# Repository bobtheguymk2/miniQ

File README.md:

# miniQ
A PCB for model rocket datalogging and control

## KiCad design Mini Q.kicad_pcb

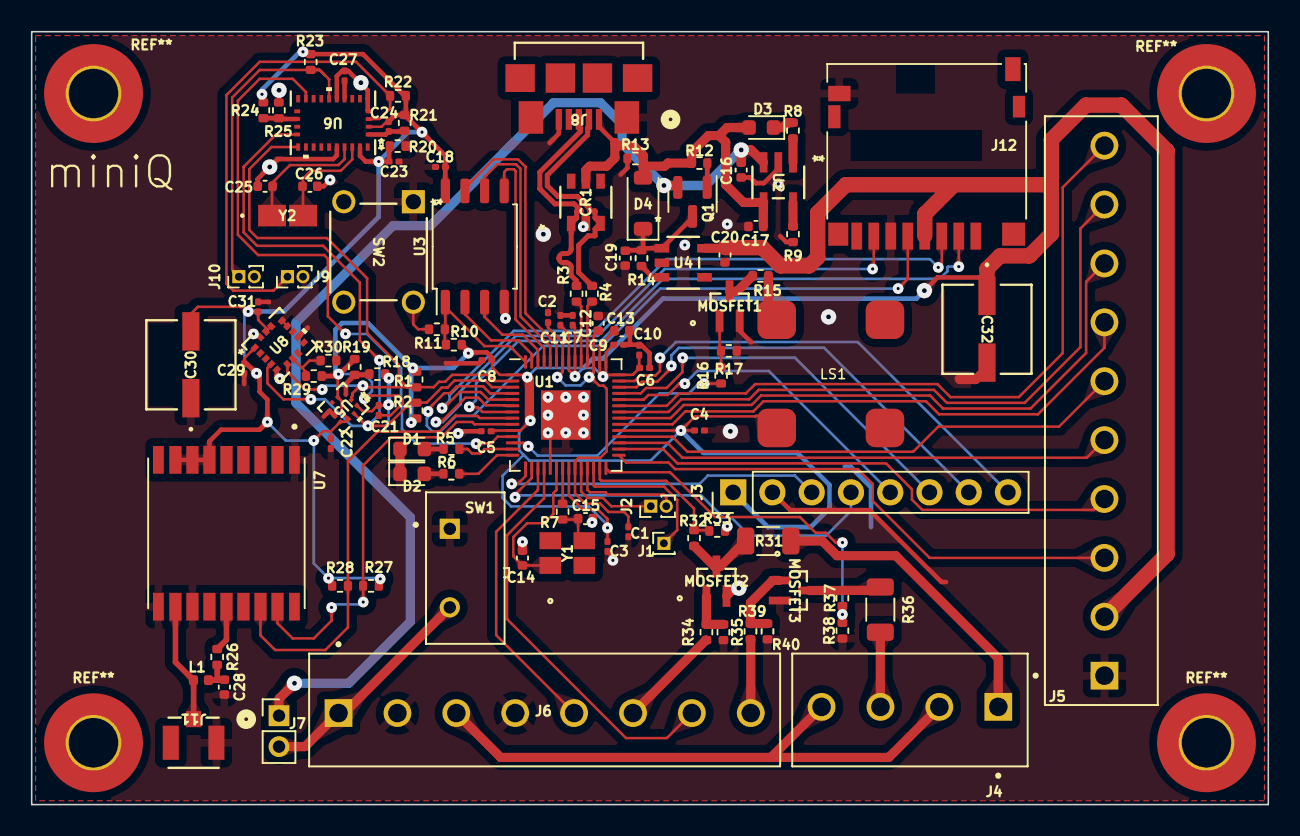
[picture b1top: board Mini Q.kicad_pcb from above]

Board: 2 copper layers, 80.0 x 50.0 mm, 107 parts (0 on the bottom side), 84 nets.

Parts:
C1, C2, C3, C4, C5, C6, C7, C8, C9, C10, C11, C18, C21, C22, C23, C24, C27, C29, C31: 100n; C_0201_0603Metric
C12, C13: 1u; C_0402_1005Metric
C14, C15, C25, C26: 15p; C_0402_1005Metric
C16, C17, C19, C20: 10u; C_0402_1005Metric
C28: 10n; C_0402_1005Metric
C30, C32: 10u; CAP_B6-SVPK_PAN-L
CR1: USBLC6-4SC6; SOT23-6L_STM
D1, D2, D3: LED; D_0603_1608Metric
D4: MBR0540; D_SOD-123
J1: Conn_01x01; PinHeader_1x01_P1.00mm_Vertical
J2: Conn_01x02; PinHeader_1x02_P1.00mm_Vertical
J3: Conn_01x08; PinHeader_1x08_P2.54mm_Vertical
J4: Pyro_Screw_Terminal_01x04; TE_1776113-4
J5: Screw_Terminal_01x10; TE_1-1776113-0
J6: Screw_Terminal_01x08; TE_1776113-8
J7: PH2.0 Female for LiPo; PinHeader_1x02_P2.00mm_Vertical
J8: USB_B_Micro; CONN_10118192-0002LF_AMP
J9: BNO_BTLDR; PinHeader_1x02_P1.00mm_Vertical
J10: BNO_NRST; PinHeader_1x02_P1.00mm_Vertical
J11: UFL Connector; CONN_RSP-122811-01_SAI
J12: Micro_SD_Card; microSD_HC_Hirose_DM3D-SF
L1: 27n; L_0402_1005Metric
LS1: TE084005-2
MOSFET1, MOSFET2, MOSFET3: DMN2058UW-7; SOT323_DMN2058UW_DIO-M
Q1: DMG3414U; SOT-23
R1, R2: 4.7k; R_0402_1005Metric
R3, R4: 27.4; R_0402_1005Metric
R5, R6: 430; R_0402_1005Metric
R7, R11, R12: 1k; R_0402_1005Metric
R8, R10, R13, R14, R17, R22, R23, R24, R29, R35, R40: 10k; R_0402_1005Metric
R9: 5.1k; R_0402_1005Metric
R15: 33; R_0402_1005Metric
R16, R34, R39: 400; R_0402_1005Metric
R18, R19, R25, R30: 0; R_0402_1005Metric
R20, R21, R27, R28: DNF; R_0402_1005Metric
R26: 10; R_0402_1005Metric
R31, R36: 6; R_1206_3216Metric
R32, R37: 100k; R_0402_1005Metric
R33, R38: 27k; R_0402_1005Metric
SW1: SW_SPST; SW_AS11CP
SW2: SW_Push; SW4_1825910-B_TEC
U1: RP2040; QFN-56-1EP_7x7mm_P0.4mm_EP3.2x3.2mm
U2: MCP73831T-2ACI/OT; SOT-23-5_MC_MCH
U3: W25Q128JVS; SOIC-8_5.23x5.23mm_P1.27mm
U4: RT9080-33GJ5; TSOT-23-5_RIT
U5: BMP390; LGA10_BMP390_BOS
U6: BNO086; QFN28_BNO086_CEV
U7: MAX-M8C-0; XCVR_MAX-M8C-0
U8: H3LIS200DLTR; TFLGA_S200DL_STM
Y1: ABM8-272-T3 -12.000MHZ; ABM8-272-T3_ABR
Y2: 32.768kHz Crystal; RT3215_RAL-M

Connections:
+1V1: C1.1, C2.1, C12.1, U1.23 (DVDD), U1.45 (VREG_VOUT), U1.50 (DVDD)
+3V3: C3.1, C4.1, C5.1, C6.1, C7.1, C8.1, C9.1, C10.1, C11.1, C13.1, C18.1, C20.1, C21.1, C22.1, C23.2, C24.2, C29.2, C30.2, C31.2, C32.1, J3.1, J5.2, J12.4 (VDD), LS1.2, R1.1, R2.1, R10.2, R19.1, R20.1, R21.1, R22.2, R23.2, R24.1, R27.1, R28.1, R29.1, U1.1 (IOVDD), U1.10 (IOVDD), U1.22 (IOVDD), U1.33 (IOVDD), U1.42 (IOVDD), U1.43 (ADC_AVDD), U1.44 (VREG_IN), U1.48 (USB_VDD), U1.49 (IOVDD), U3.8 (VCC), U4.5 (VOUT), U5.1 (VDDIO), U5.6 (CSB), U5.10 (VDD), U6.3 (VDD), U6.28 (VDDIO), U7.6 (V_BCKP), U7.7 (VCC_IO), U7.8 (VCC), U8.1 (Vdd_IO), U8.14 (Vdd), U8.15 (Reserved)
+12V: J4.2, J4.4, J6.3
+BATT: C16.1, J7.1, Q1.2 (S), U2.3 (VBAT)
/GPIO18_PWM1A_TVC/FINS: J5.3, U1.29 (GPIO18)
/GPIO19_PWM1B_TVC/FINS: J5.4, U1.30 (GPIO19)
/GPIO20_PWM2A_TVC/FINS: J5.5, U1.31 (GPIO20)
/GPIO21_PWM2B_TVC/FINS: J5.6, U1.32 (GPIO21)
/GPIO22_PWM3A_TVC/FINS: J5.7, U1.34 (GPIO22)
/GPIO23_PWM3B_TVC/FINS: J5.8, U1.35 (GPIO23)
/GPIO24_PWM4A_ROLL: J5.9, U1.36 (GPIO24)
/GPIO25_PWM4B_ROLL: J5.10, U1.37 (GPIO25)
/QSPI_SCLK: U1.52 (QSPI_SCLK), U3.6 (CLK)
/QSPI_SD0: U1.53 (QSPI_SD0), U3.5 (DI(IO0))
/QSPI_SD1: U1.55 (QSPI_SD1), U3.2 (DO(IO1))
/QSPI_SD2: U1.54 (QSPI_SD2), U3.3 (IO2)
/QSPI_SD3: U1.51 (QSPI_SD3), U3.7 (IO3)
/QSPI_SS: R10.1, R11.2, U1.56 (QSPI_SS), U3.1 (~CS)
/SWTCH+: J6.1, J7.2, SW1.3 (B)
/USB_D+: CR1.1 (I/O1), J8.3 (D+), R3.1
/USB_D-: CR1.3 (I/O2), J8.2 (D-), R4.1
Fet_apogee: J4.1, R31.2
Fet_apogee_sense: R32.2, R33.1, U1.27 (GPIO16)
Fet_main: J4.3, R36.2
Fet_main_sense: R37.2, R38.1, U1.28 (GPIO17)
GND: C1.2, C2.2, C3.2, C4.2, C5.2, C6.2, C7.2, C8.2, C9.2, C10.2, C11.2, C12.2, C13.2, C14.2, C15.2, C16.2, C17.2, C18.2, C19.2, C20.2, C21.2, C22.2, C23.1, C24.1, C25.2, C26.2, C27.2, C28.2, C29.1, C30.1, C31.1, C32.2, CR1.2 (GND), D1.1 (K), D2.1 (K), J3.2, J5.1, J6.2, J6.4, J8.5 (GND), J8.6 (Shield), J9.2, J10.2, J11.2 (Ext), J12.6 (VSS), J12.9 (SHIELD), MOSFET1.2 (S), MOSFET2.2 (S), MOSFET3.2 (S), R9.2, R13.1, R17.1, R18.2, R20.2, R21.2, R25.2, R30.2, R33.2, R35.1, R38.2, R40.1, SW1.1 (A), SW2.1, U1.19 (TESTEN), U1.57 (GND), U2.2 (VSS), U3.4 (GND), U4.2 (GND), U5.3 (VSS), U5.8 (VSS), U5.9 (VSS), U6.2 (GND), U6.5 (PS1), U6.6 (PS0/WAKE), U6.10 (CLKSEL0), U6.25 (GND), U7.1 (GND), U7.10 (GND), U7.12 (GND), U8.5 (GND), U8.10 (Reserved), U8.12 (GND), U8.13 (GND), U8.16 (GND)
GPIO0_I2CSDA_BMPBNO: R1.2, U1.2 (GPIO0), U5.4 (SDI), U6.20 (H_SDA/H_MISO/TX), U8.6 (SDA/SDI/SDO)
GPIO1_I2CSCL_BMPBNO: R2.2, U1.3 (GPIO1), U5.2 (SCK), U6.19 (H_SCL/SCK/RX), U8.4 (SCL/SPC)
GPIO2_SPISCK_mSD: J12.5 (CLK), U1.4 (GPIO2)
GPIO3_SPIMOSI_mSD: J12.3 (CMD), U1.5 (GPIO3)
GPIO4_SPIMISO_mSD: J12.7 (DAT0), U1.6 (GPIO4)
GPIO5_SPICSn_mSD: J12.2 (DAT3/CD), U1.7 (GPIO5)
GPIO6_I2CSDA_GNSS: R28.2, U1.8 (GPIO6), U7.16 (SDA)
GPIO7_I2CSCL_GNSS: R27.2, U1.9 (GPIO7), U7.17 (SCL)
GPIO8_GPIOWake_BNO: U1.11 (GPIO8), U6.14 (H_INTN)
GPIO9_Transistor_Beeper: R16.1, U1.12 (GPIO9)
GPIO12_Reset_RF(Transciever): J3.3, U1.15 (GPIO12)
GPIO13_DIO0_RF(Transciever): J3.4, U1.16 (GPIO13)
GPIO26_SPISCK_RF(Transciever): J3.5, U1.38 (GPIO26_ADC0)
GPIO27_SPITX_RF(Transciever): J3.6, U1.39 (GPIO27_ADC1)
GPIO28_SPIRX_RF(Transciever): J3.7, U1.40 (GPIO28_ADC2)
GPIO29_SPICSn_RF(Transciever): J3.8, U1.41 (GPIO29_ADC3)
unnamed: C15.1, R7.1, Y1.3
unnamed: C28.1, L1.2, R26.2
unnamed: D1.2 (A), R5.2
unnamed: D2.2 (A), R6.2
unnamed: D3.1 (K), R8.2
unnamed: C19.1, D4.1 (K), Q1.3 (D), R14.2, U4.1 (VIN)
unnamed: J1.1, U1.26 (RUN)
unnamed: J2.1, U1.24 (SWCLK)
unnamed: J2.2, U1.25 (SWD)
unnamed: J9.1, R22.1, U6.4 (BOOTN)
unnamed: J10.1, R23.1, U6.11 (NRST)
unnamed: J11.1 (In), L1.1, U7.11 (RF_IN)
unnamed: LS1.1, R15.1
unnamed: MOSFET1.3 (D), R15.2
unnamed: MOSFET1.1 (G), R16.2, R17.2
unnamed: MOSFET2.3 (D), R31.1, R32.1
unnamed: MOSFET2.1 (G), R34.2, R35.2
unnamed: MOSFET3.3 (D), R36.1, R37.1
unnamed: MOSFET3.1 (G), R39.2, R40.2
unnamed: Q1.1 (G), R12.2
unnamed: R11.1, SW2.2
unnamed: R5.1, U1.13 (GPIO10)
unnamed: R6.1, U1.14 (GPIO11)
unnamed: R4.2, U1.46 (USB_DM)
unnamed: R3.2, U1.47 (USB_DP)
unnamed: C14.1, U1.20 (XIN), Y1.1
unnamed: R7.2, U1.21 (XOUT)
unnamed: R9.1, U2.5 (PROG)
unnamed: R8.1, U2.1 (STAT)
unnamed: R14.1, U4.3 (EN)
unnamed: R18.1, R19.2, U5.5 (SDO)
unnamed: C27.1, U6.9 (CAP)
unnamed: R24.2, R25.1, U6.17 (SA0/H_MOSI)
unnamed: C26.1, U6.27 (XIN32), Y2.2
unnamed: C25.1, U6.26 (XOUT32/CLKSEL1), Y2.1
unnamed: R26.1, U7.14 (VCC_RF)
unnamed: R29.2, R30.1, U8.7 (SDO/SA0)
Pyro1_Fet_Arm+: J6.5, U1.17 (GPIO14)
Pyro1_Fet_Arm-: J6.6, R34.1
Pyro2_Fet_Arm+: J6.7, U1.18 (GPIO15)
Pyro2_Fet_Arm-: J6.8, R39.1
VBUS: C17.1, CR1.5 (VBUS), D3.2 (A), D4.2 (A), J8.1 (VBUS), R12.1, R13.2, U2.4 (VDD)
